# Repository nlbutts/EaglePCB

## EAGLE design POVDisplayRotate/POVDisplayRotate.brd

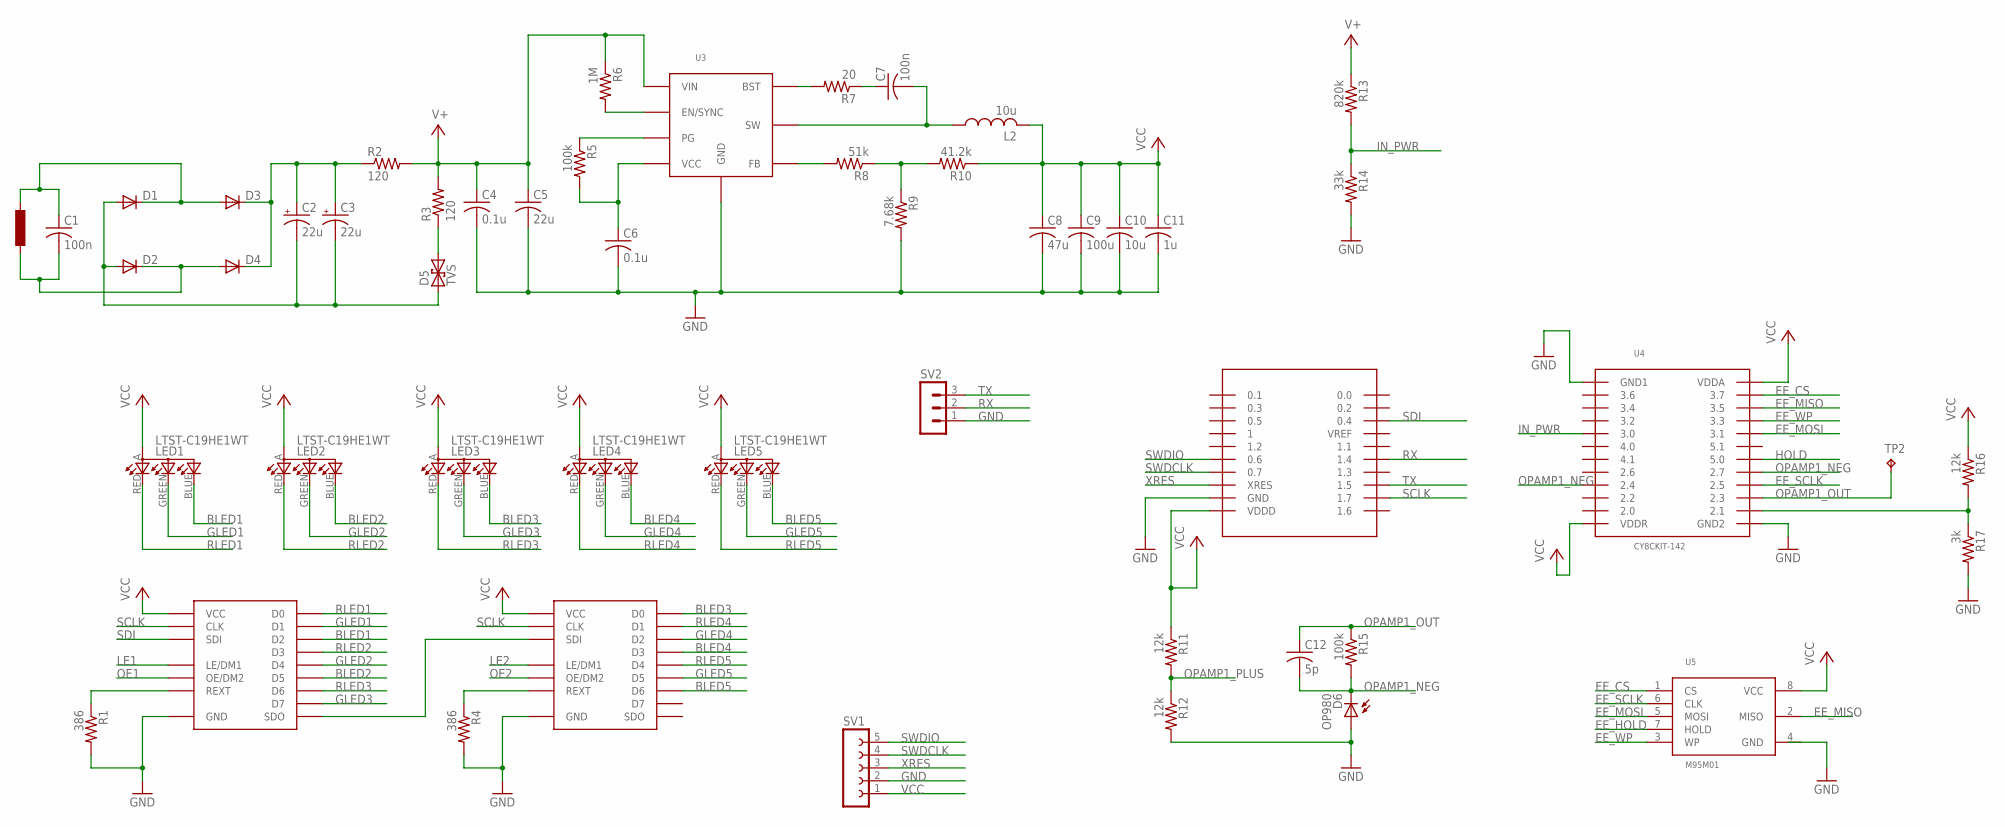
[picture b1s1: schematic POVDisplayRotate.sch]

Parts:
C1: 100n; C1210
C2, C3: 22u; PANASONIC_C; DIGIKEY PCE5022CT-ND
C4, C6: 0.1u; C0603; DIGIKEY 490-6505-1-ND
C5: 22u; C0805; DIGIKEY 445-14428-1-ND
C7: 100n; C0603
C8: 47u; C0603
C9: 100u; C1210
C10: 10u; C0603
C11: 1u; C0603
C12: 5p; C0603
D1, D2, D3, D4: DIODE-SOD123; SOD123; DIGIKEY B0540W-FDICT-ND
D5: TVS; SMB; DIGIKEY 1SMB28CAT3GOSCT-ND
D6: OP980; PLCC-2; DIGIKEY 365-1908-1-ND
L2: 10u; L1812; DIGIKEY 587-1625-1-ND
LED1, LED2, LED3, LED4, LED5: LTST-C19HE1WT; DIGIKEY 160-2162-1-ND
R1, R4: 386; R0603; DIGIKEY P0.0GCT-ND
R2, R3: 120; R0603; DIGIKEY P0.0GCT-ND
R5, R15: 100k; R0603; DIGIKEY P0.0GCT-ND
R6: 1M; R0603; DIGIKEY P0.0GCT-ND
R7: 20; R0603; DIGIKEY P0.0GCT-ND
R8: 51k; R0603; DIGIKEY P0.0GCT-ND
R9: 7.68k; R0603; DIGIKEY P0.0GCT-ND
R10: 41.2k; R0603; DIGIKEY P0.0GCT-ND
R11, R12, R16: 12k; R0603; DIGIKEY P0.0GCT-ND
R13: 820k; R0603; DIGIKEY P0.0GCT-ND
R14: 33k; R0603; DIGIKEY P0.0GCT-ND
R17: 3k; R0603; DIGIKEY P0.0GCT-ND
SV1: FE05-1
SV2: MA03-1
TP2: TPB1,27; B1,27
U1, U2: STP08DP05; SSOP16_EPAD; DIGIKEY 497-6119-1-ND
U3: MPQ4420Q; SOT-23-8; DIGIKEY 1589-1293-1-ND
U4: CY8CKIT-142
U5: M95M01; SO-08; DIGIKEY 497-14359-1-ND

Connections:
BLED1: LED1.BLUE (CBLUE), U1.7 (D2)
BLED2: LED2.BLUE (CBLUE), U1.10 (D5)
BLED3: LED3.BLUE (CBLUE), U2.5 (D0)
BLED4: LED4.BLUE (CBLUE), U2.8 (D3)
BLED5: LED5.BLUE (CBLUE), U2.11 (D6)
DAC_OUT: R16.2, R17.1, U4.2.1
EE_CS: U4.3.7, U5.1 (CS)
EE_HOLD: U5.7 (HOLD)
EE_MISO: U4.3.5, U5.2 (MISO)
EE_MOSI: U4.3.1, U5.5 (MOSI)
EE_SCLK: U4.2.5, U5.6 (CLK)
EE_WP: U4.3.3, U5.3 (WP)
GLED1: LED1.GREEN (CGREEN), U1.6 (D1)
GLED2: LED2.GREEN (CGREEN), U1.9 (D4)
GLED3: LED3.GREEN (CGREEN), U1.12 (D7)
GLED4: LED4.GREEN (CGREEN), U2.7 (D2)
GLED5: LED5.GREEN (CGREEN), U2.10 (D5)
GND: C4.2, C5.2, C6.2, C8.2, C9.2, C10.2, C11.2, D6.P$1 (A), R1.2, R4.2, R9.2, R12.2, R14.2, R17.2, SV1.2, SV2.1, U1.1 (GND), U1.GND, U2.1 (GND), U2.GND, U3.4 (GND), U4.GND, U4.GND1, U4.GND2, U5.4 (GND)
HOLD: U4.5.0
IN_PWR: R13.2, R14.1, U4.3.0
LE1: U1.4 (LE/DM1)
LE2: U2.4 (LE/DM1)
unnamed: C6.1, R5.2, U3.7 (VCC)
unnamed: R6.2, U3.6 (EN/SYNC)
unnamed: C2.+, C3.+, D3.C, D4.C, R2.1
unnamed: R8.2, U3.8 (FB)
unnamed: R8.1, R9.1, R10.2
unnamed: R1.1, U1.15 (REXT)
unnamed: R7.2, U3.5 (BST)
unnamed: C7.1, R7.1
unnamed: R4.1, U2.15 (REXT)
unnamed: D5.C (2), R3.1
unnamed: R5.1, U3.1 (PG)
unnamed: C2.-, C3.-, D1.A, D2.A, D5.A (1)
unnamed: U1.14 (SDO), U2.2 (SDI)
NEG_COIL: C1.2, D2.C, D4.A
OE1: U1.13 (OE/DM2)
OE2: U2.13 (OE/DM2)
OPAMP1_NEG: C12.2, D6.P$2 (C), R15.2, U4.2.4, U4.2.7
OPAMP1_OUT: C12.1, R15.1, TP2.TP, U4.2.3
OPAMP1_PLUS: R11.2, R12.1
POS_COIL: C1.1, D1.C, D3.A
RLED1: LED1.RED (CRED), U1.5 (D0)
RLED2: LED2.RED (CRED), U1.8 (D3)
RLED3: LED3.RED (CRED), U1.11 (D6)
RLED4: LED4.RED (CRED), U2.6 (D1)
RLED5: LED5.RED (CRED), U2.9 (D4)
RX: SV2.2, U4.1.4
SCLK: U1.3 (CLK), U2.3 (CLK), U4.1.7
SDI: U1.2 (SDI), U4.0.4
SWDCLK: SV1.4, U4.0.7
SWDIO: SV1.5, U4.0.6
SWOUT: C7.2, L2.1, U3.3 (SW)
TX: SV2.3, U4.1.5
V+: C4.1, C5.1, R2.2, R3.2, R6.1, R13.1, U3.2 (VIN)
VCC: C8.1, C9.1, C10.1, C11.1, L2.2, LED1.A, LED2.A, LED3.A, LED4.A, LED5.A, R10.1, R11.1, R16.1, SV1.1, U1.16 (VCC), U2.16 (VCC), U4.VDDA, U4.VDDD, U4.VDDR, U5.8 (VCC)
XRES: SV1.3, U4.XRES

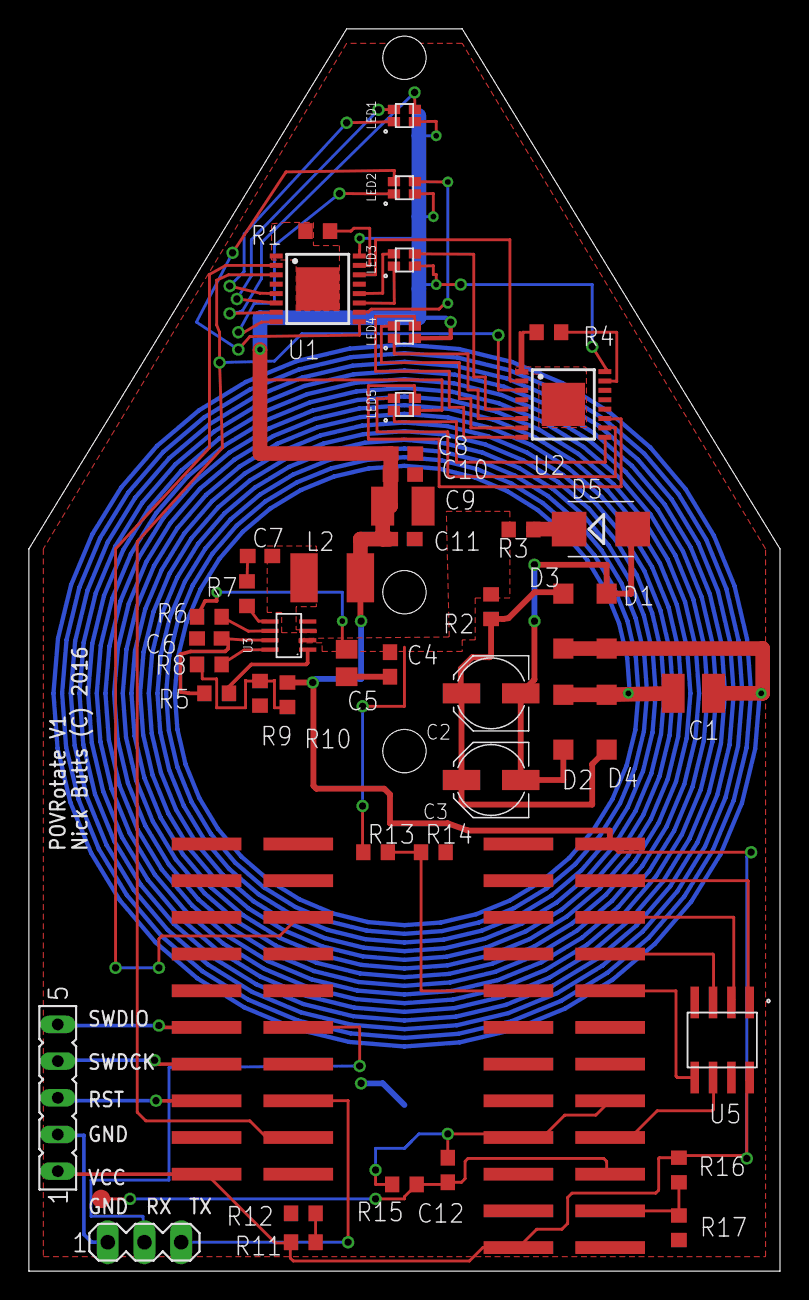
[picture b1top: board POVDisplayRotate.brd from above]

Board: 2 copper layers, 52.0 x 86.0 mm, 49 parts (1 on the bottom side), 51 nets.

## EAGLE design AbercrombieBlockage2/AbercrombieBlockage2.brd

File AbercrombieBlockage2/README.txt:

This is deprecated and has been moved to the Bitbucket Appareo location.

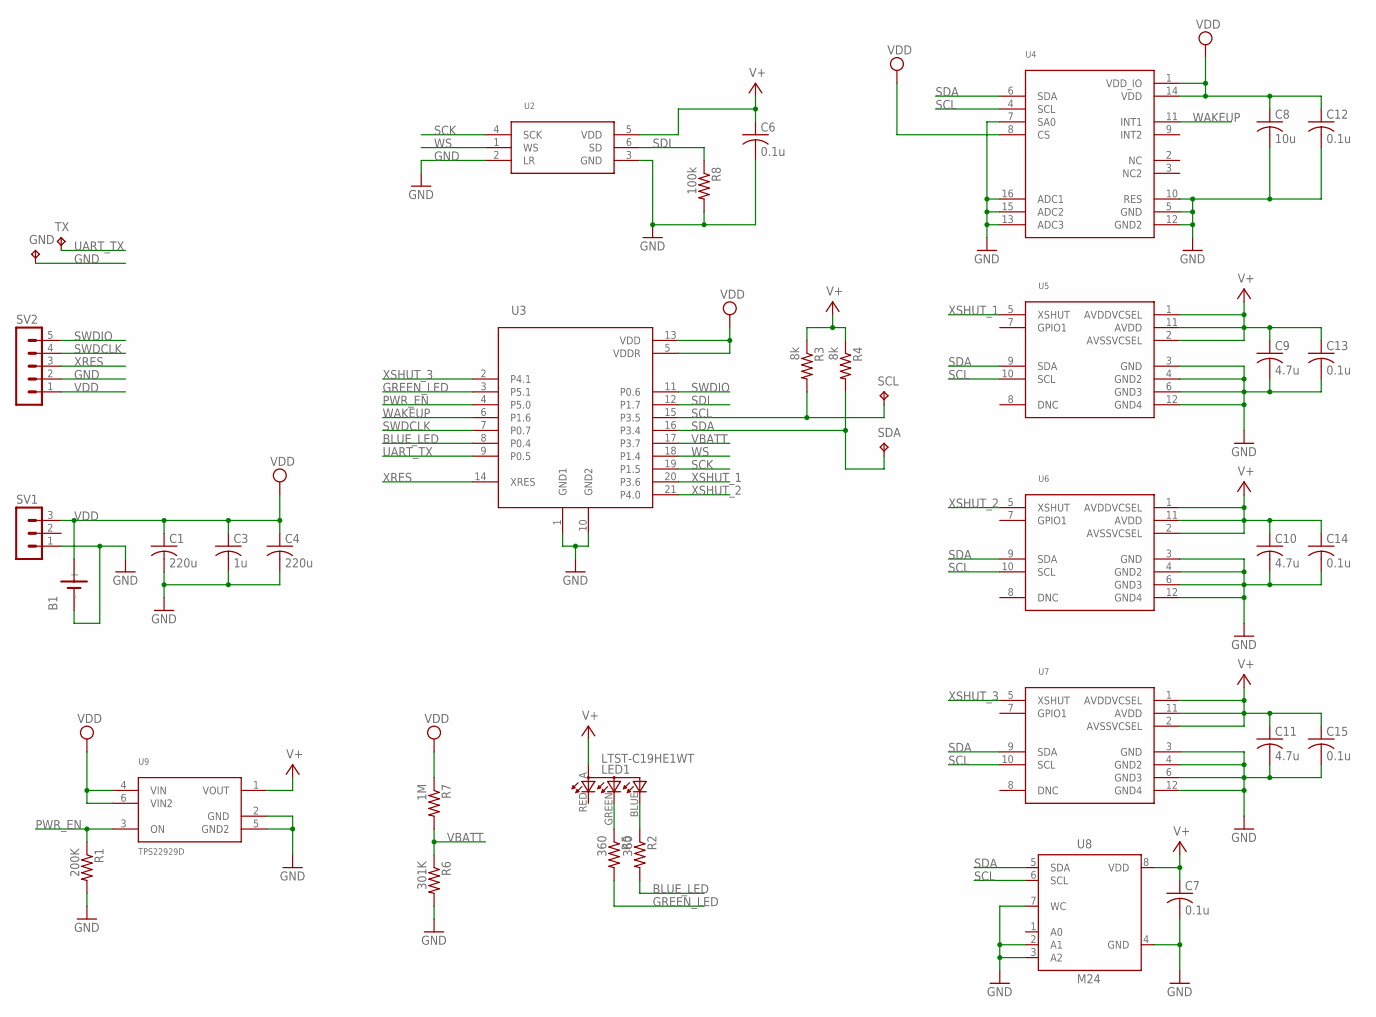
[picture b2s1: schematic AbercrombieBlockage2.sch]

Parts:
B1: BU2032
C1: 220u; C1210; DIGIKEYY 490-13250-1-ND
C3: 1u; C0603
C4: 220u; C1210
C6, C7, C12, C13, C14, C15: 0.1u; C0603
C8: 10u; C0603
C9, C10, C11: 4.7u; C0603
GND: TPB1,27; B1,27
LED1: LTST-C19HE1WT; DIGIKEY 160-2162-1-ND
R1: 200K; R0603
R2, R5: 360; R0603
R3, R4: 8k; R0603
R6: 301K; R0603
R7: 1M; R0603
R8: 100k; R0603
SCL: TPB1,27; B1,27
SDA: TPB1,27; B1,27
SV1: MA03-1
SV2: MA05-1; DIGIKEY 952-2246-ND
TX: TPB1,27; B1,27
U2: ICS-43434; DIGIKEY 1428-1066-1-ND
U3: CYBLE-022001-00; DIGIKEY 428-3566-PROMO-ND
U4: LIS3DH; LGA-16; DIGIKEY 497-10613-1-ND
U5, U6, U7: VL53L0X; DIGIKEY 497-16538-1-ND
U8: M24; SO-08; DIGIKEY 497-6351-1-ND
U9: TPS22929D; SOT-23-6

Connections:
BLUE_LED: R2.2, U3.8 (P0.4)
GND: B1.NEG (-), C1.2, C3.2, C4.2, C6.2, C7.2, C8.2, C9.2, C10.2, C11.2, C12.2, C13.2, C14.2, C15.2, GND.TP, R1.2, R6.2, R8.2, SV1.1, SV2.2, U2.2 (LR), U2.3 (GND), U3.1 (GND1), U3.10 (GND2), U4.5 (GND), U4.7 (SA0), U4.10 (RES), U4.12 (GND2), U4.13 (ADC3), U4.15 (ADC2), U4.16 (ADC1), U5.3 (GND), U5.4 (GND2), U5.6 (GND3), U5.12 (GND4), U6.3 (GND), U6.4 (GND2), U6.6 (GND3), U6.12 (GND4), U7.3 (GND), U7.4 (GND2), U7.6 (GND3), U7.12 (GND4), U8.2 (A1), U8.3 (A2), U8.4 (GND), U8.7 (WC), U9.2 (GND), U9.5 (GND2)
GREEN_LED: R5.2, U3.3 (P5.1)
unnamed: LED1.BLUE (CBLUE), R2.1
unnamed: LED1.GREEN (CGREEN), R5.1
PWR_EN: R1.1, U3.4 (P5.0), U9.3 (ON)
SCK: U2.4 (SCK), U3.19 (P1.5)
SCL: R3.2, SCL.TP, U3.15 (P3.5), U4.4 (SCL), U5.10 (SCL), U6.10 (SCL), U7.10 (SCL), U8.6 (SCL)
SDA: R4.2, SDA.TP, U3.16 (P3.4), U4.6 (SDA), U5.9 (SDA), U6.9 (SDA), U7.9 (SDA), U8.5 (SDA)
SDI: R8.1, U2.6 (SD), U3.12 (P1.7)
SWDCLK: SV2.4, U3.7 (P0.7)
SWDIO: SV2.5, U3.11 (P0.6)
UART_TX: TX.TP, U3.9 (P0.5)
V+: C6.1, C7.1, C9.1, C10.1, C11.1, C13.1, C14.1, C15.1, LED1.A, R3.1, R4.1, U2.5 (VDD), U5.1 (AVDDVCSEL), U5.2 (AVSSVCSEL), U5.11 (AVDD), U6.1 (AVDDVCSEL), U6.2 (AVSSVCSEL), U6.11 (AVDD), U7.1 (AVDDVCSEL), U7.2 (AVSSVCSEL), U7.11 (AVDD), U8.8 (VDD), U9.1 (VOUT)
VBATT: R6.1, R7.2, U3.17 (P3.7)
VDD: B1.PLUS (+), C1.1, C3.1, C4.1, C8.1, C12.1, R7.1, SV1.3, SV2.1, U3.5 (VDDR), U3.13 (VDD), U4.1 (VDD_IO), U4.8 (CS), U4.14 (VDD), U9.4 (VIN), U9.6 (VIN2)
WAKEUP: U3.6 (P1.6), U4.11 (INT1)
WS: U2.1 (WS), U3.18 (P1.4)
XRES: SV2.3, U3.14 (XRES)
XSHUT_1: U3.20 (P3.6), U5.5 (XSHUT)
XSHUT_2: U3.21 (P4.0), U6.5 (XSHUT)
XSHUT_3: U3.2 (P4.1), U7.5 (XSHUT)

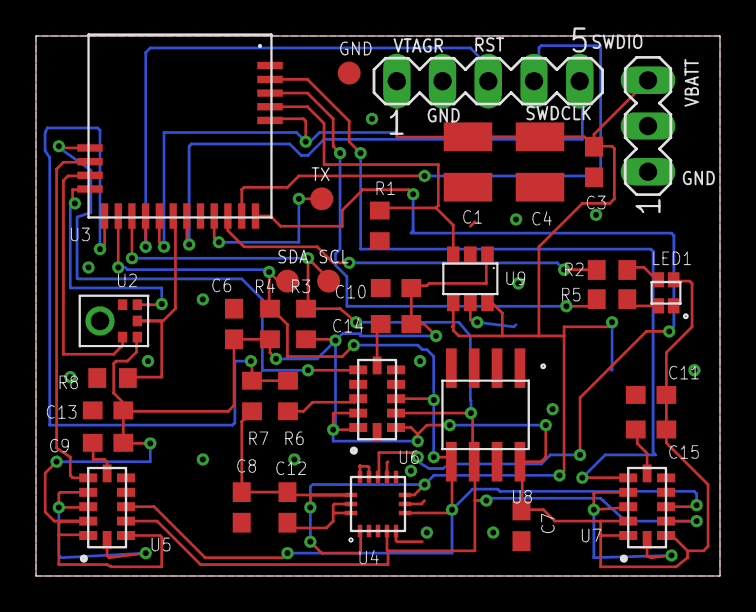
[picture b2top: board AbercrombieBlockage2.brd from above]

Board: 2 copper layers, 38.0 x 30.0 mm, 37 parts (1 on the bottom side), 22 nets.

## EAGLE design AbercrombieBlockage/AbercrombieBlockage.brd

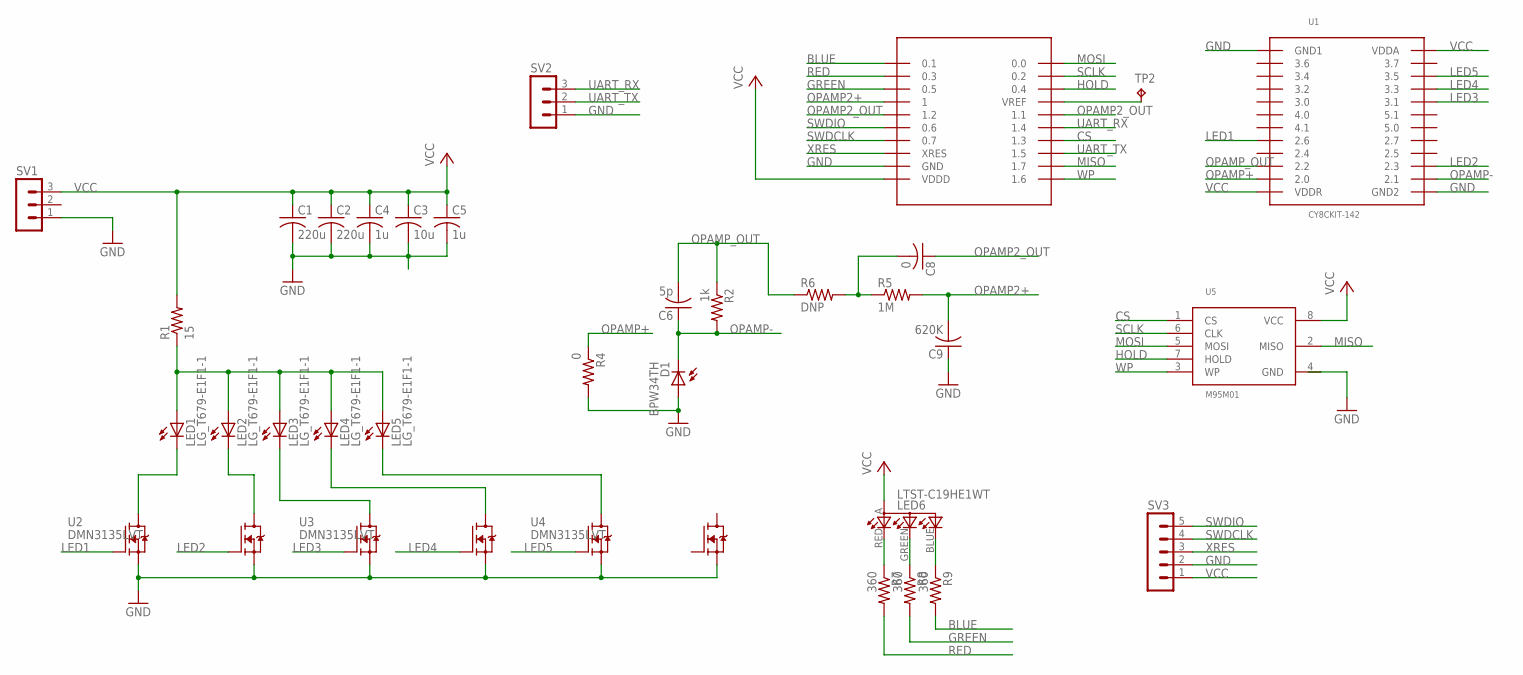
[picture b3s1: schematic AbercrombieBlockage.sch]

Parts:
C1, C2: 220u; C1210
C3: 10u; C1210
C4, C5: 1u; C0603
C6: 5p; C0603
C8: 0; C0603
C9: 620K; C0603
D1: BPW34TH; BPW34
LED1, LED2, LED3, LED4, LED5: LG_T679-E1F1-1; PLCC2; DIGIKEY VSMY3850-GS08CT-ND
LED6: LTST-C19HE1WT
R1: 15; R2010; DIGIKEY_100_OHM YAG3381CT-ND
R2: 1k; R0603
R4: 0; R0603
R5: 1M; R0603
R6: DNP; R0603
R7, R8, R9: 360; R0603
SV1, SV2: MA03-1
SV3: MA05-1
TP2: TPB1,27; B1,27
U1: CY8CKIT-142
U2, U3, U4: DMN3135LVT; SOT-23-6; DIGIKEY DMN3135LVT-7DICT-ND
U5: M95M01; SO-08; DIGIKEY 497-14359-1-ND

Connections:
BLUE: R9.2, U1.0.1
CS: U1.1.3, U5.1 (CS)
GND: C1.2, C2.2, C3.2, C4.2, C5.2, C9.1, D1.A, R4.2, SV1.1, SV2.1, SV3.2, U1.GND, U1.GND1, U1.GND2, U2.2 (S2), U2.5 (S1), U3.2 (S2), U3.5 (S1), U4.2 (S2), U4.5 (S1), U5.4 (GND)
GREEN: R8.2, U1.0.5
HOLD: U1.0.4, U5.7 (HOLD)
LED1: U1.2.6, U2.1 (G1)
LED2: U1.2.3, U2.3 (G2)
LED3: U1.3.1, U3.1 (G1)
LED4: U1.3.3, U3.3 (G2)
LED5: U1.3.5, U4.1 (G1)
MISO: U1.1.7, U5.2 (MISO)
MOSI: U1.0.0, U5.5 (MOSI)
unnamed: LED1.A, LED2.A, LED3.A, LED4.A, LED5.A, R1.1
unnamed: LED1.C, U2.6 (D1)
unnamed: LED2.C, U2.4 (D2)
unnamed: LED3.C, U3.6 (D1)
unnamed: LED4.C, U3.4 (D2)
unnamed: LED5.C, U4.6 (D1)
unnamed: C8.2, R5.1, R6.2
unnamed: TP2.TP, U1.VREF
unnamed: LED6.RED (CRED), R7.1
unnamed: LED6.GREEN (CGREEN), R8.1
unnamed: LED6.BLUE (CBLUE), R9.1
OPAMP2+: C9.2, R5.2, U1.1
OPAMP2_OUT: C8.1, U1.1.1, U1.1.2
OPAMP+: R4.1, U1.2.0
OPAMP-: C6.1, D1.C, R2.2, U1.2.1
OPAMP_OUT: C6.2, R2.1, R6.1, U1.2.2
RED: R7.2, U1.0.3
SCLK: U1.0.2, U5.6 (CLK)
SWDCLK: SV3.4, U1.0.7
SWDIO: SV3.5, U1.0.6
UART_RX: SV2.3, U1.1.4
UART_TX: SV2.2, U1.1.5
VCC: C1.1, C2.1, C3.1, C4.1, C5.1, LED6.A, R1.2, SV1.3, SV3.1, U1.VDDA, U1.VDDD, U1.VDDR, U5.8 (VCC)
WP: U1.1.6, U5.3 (WP)
XRES: SV3.3, U1.XRES

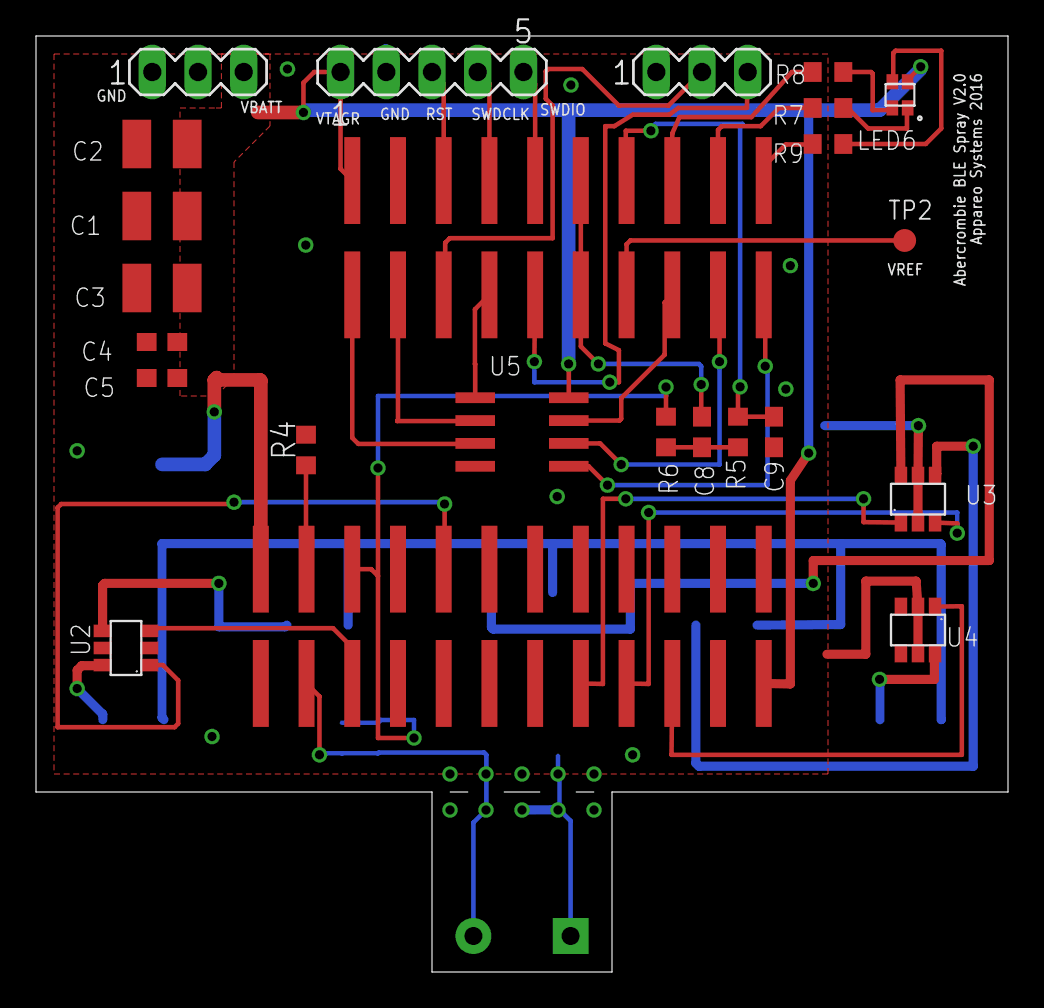
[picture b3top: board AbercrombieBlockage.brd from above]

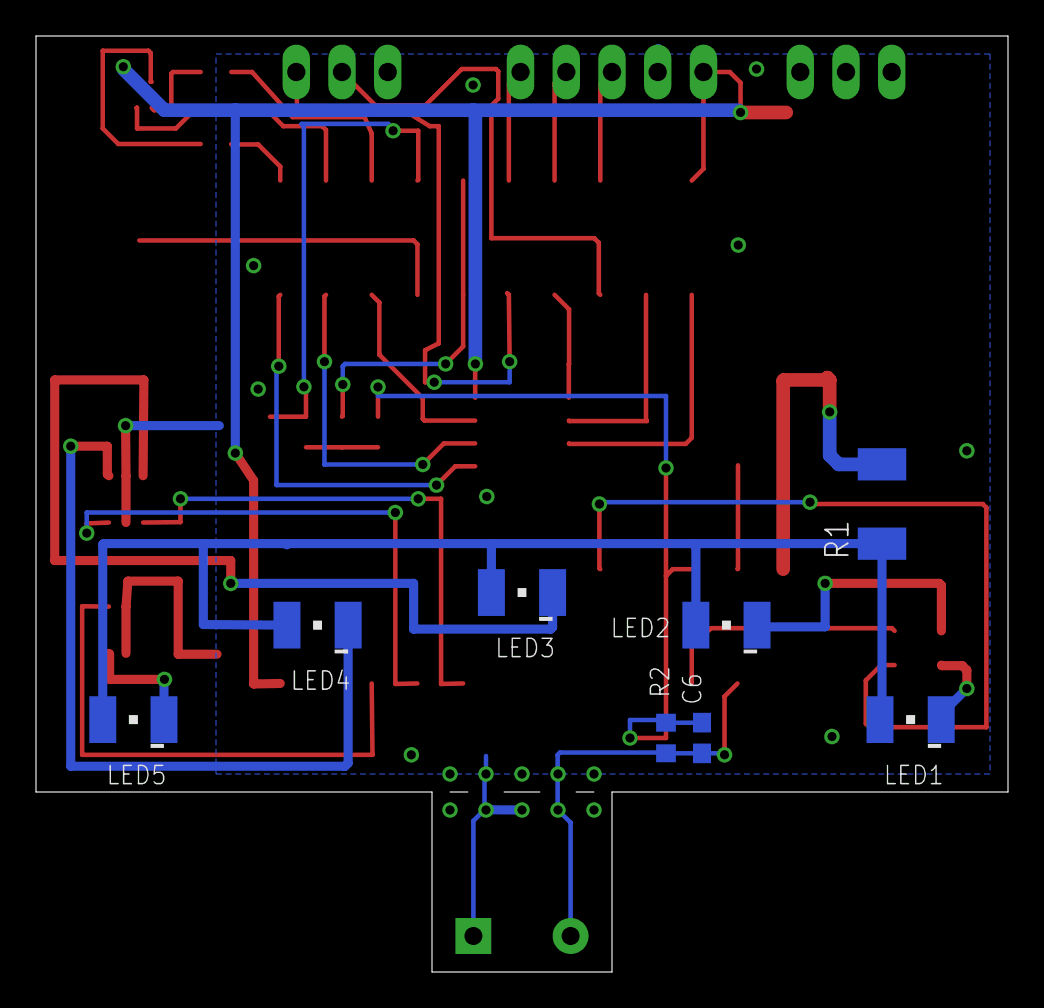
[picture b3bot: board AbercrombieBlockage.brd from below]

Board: 2 copper layers, 54.0 x 52.0 mm, 32 parts (9 on the bottom side), 37 nets.

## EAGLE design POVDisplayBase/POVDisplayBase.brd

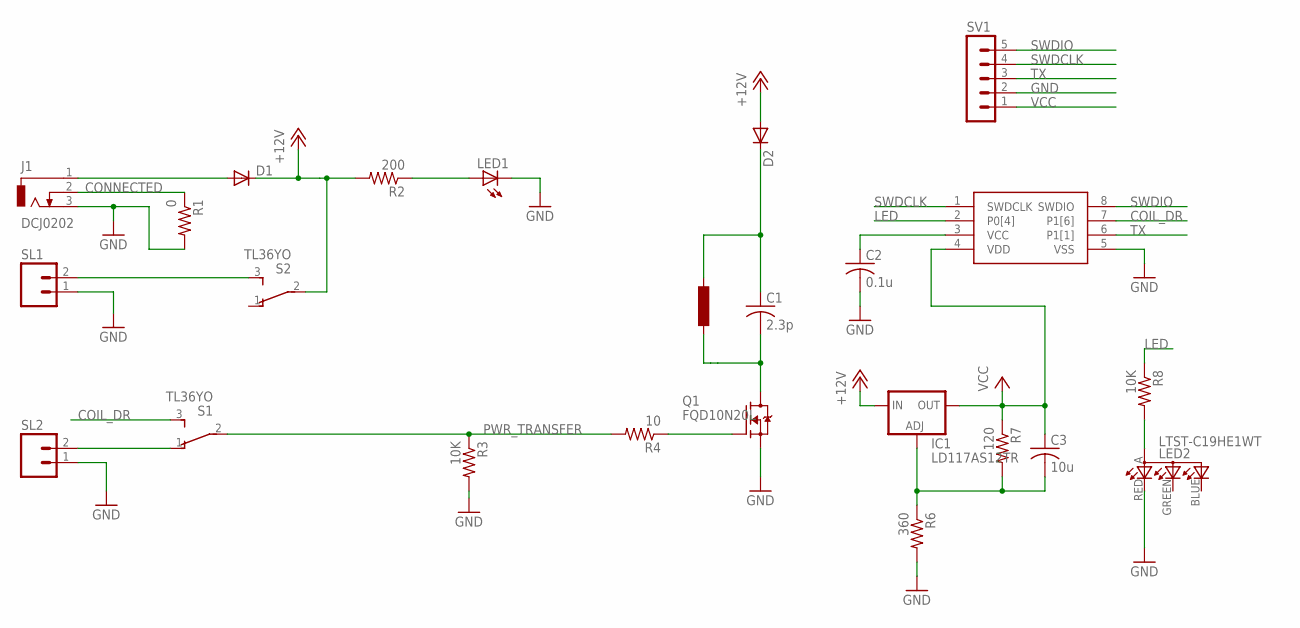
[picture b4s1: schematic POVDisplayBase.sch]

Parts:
C1: 2.3p; C1210
C2: 0.1u; C0603
C3: 10u; C0603
D1: DIODE-DO-214AC; DO-214AC; DIGIKEY 641-1707-1-ND
D2: DIODE-SMC; SMC; DIGIKEY S5KC-FDICT-ND
IC1: LD117AS12TR; SOT223
J1: DCJ0202; DIGIKEY CP-002B-ND
LED1: LEDCHIPLED_1206; CHIPLED_1206; DIGIKEY 1080-1346-1-ND
LED2: LTST-C19HE1WT
Q1: FQD10N20L; TO252; DIGIKEY FQD10N20LTMCT-ND
R1: 0; R0603; DIGIKEY P180GCT-ND
R2: 200; R0603; DIGIKEY P180GCT-ND
R3, R8: 10K; R0603; DIGIKEY P180GCT-ND
R4: 10; R0603; DIGIKEY P180GCT-ND
R6: 360; R0603; DIGIKEY P180GCT-ND
R7: 120; R0603; DIGIKEY P180GCT-ND
S1, S2: TL36YO; TL3XYO; DIGIKEY 450-1603-ND
SL1, SL2: M02; 02P
SV1: MA05-1
U1: CY8C4013SXI-400; SOIC08

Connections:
+12V: D1.C, D2.A, IC1.3 (IN), R2.2, S2.2
COIL_DR: S1.3 (S), U1.7 (P1[6])
CONNECTED: J1.2, R1.1
GND: C2.2, J1.3, LED1.C, LED2.RED (CRED), Q1.2 (S), R1.2, R3.2, R6.2, SL1.1, SL2.1, SV1.2, U1.5 (VSS)
LED: R8.1, U1.2 (P0[4])
unnamed: Q1.1 (G), R4.1
unnamed: LED1.A, R2.1
unnamed: S2.3 (S), SL1.2
unnamed: D1.A, J1.1
unnamed: C3.2, IC1.1 (ADJ), R6.1, R7.2
unnamed: LED2.A, R8.2
unnamed: C2.1, U1.3 (VCC)
unnamed: S1.1 (O), SL2.2
NEG_COIL: C1.2, Q1.3 (D)
POS_COIL: C1.1, D2.C
PWR_TRANSFER: R3.1, R4.2, S1.2
SWDCLK: SV1.4, U1.1 (SWDCLK)
SWDIO: SV1.5, U1.8 (SWDIO)
TX: SV1.3, U1.6 (P1[1])
VCC: C3.1, IC1.4 (OUT), R7.1, SV1.1, U1.4 (VDD)

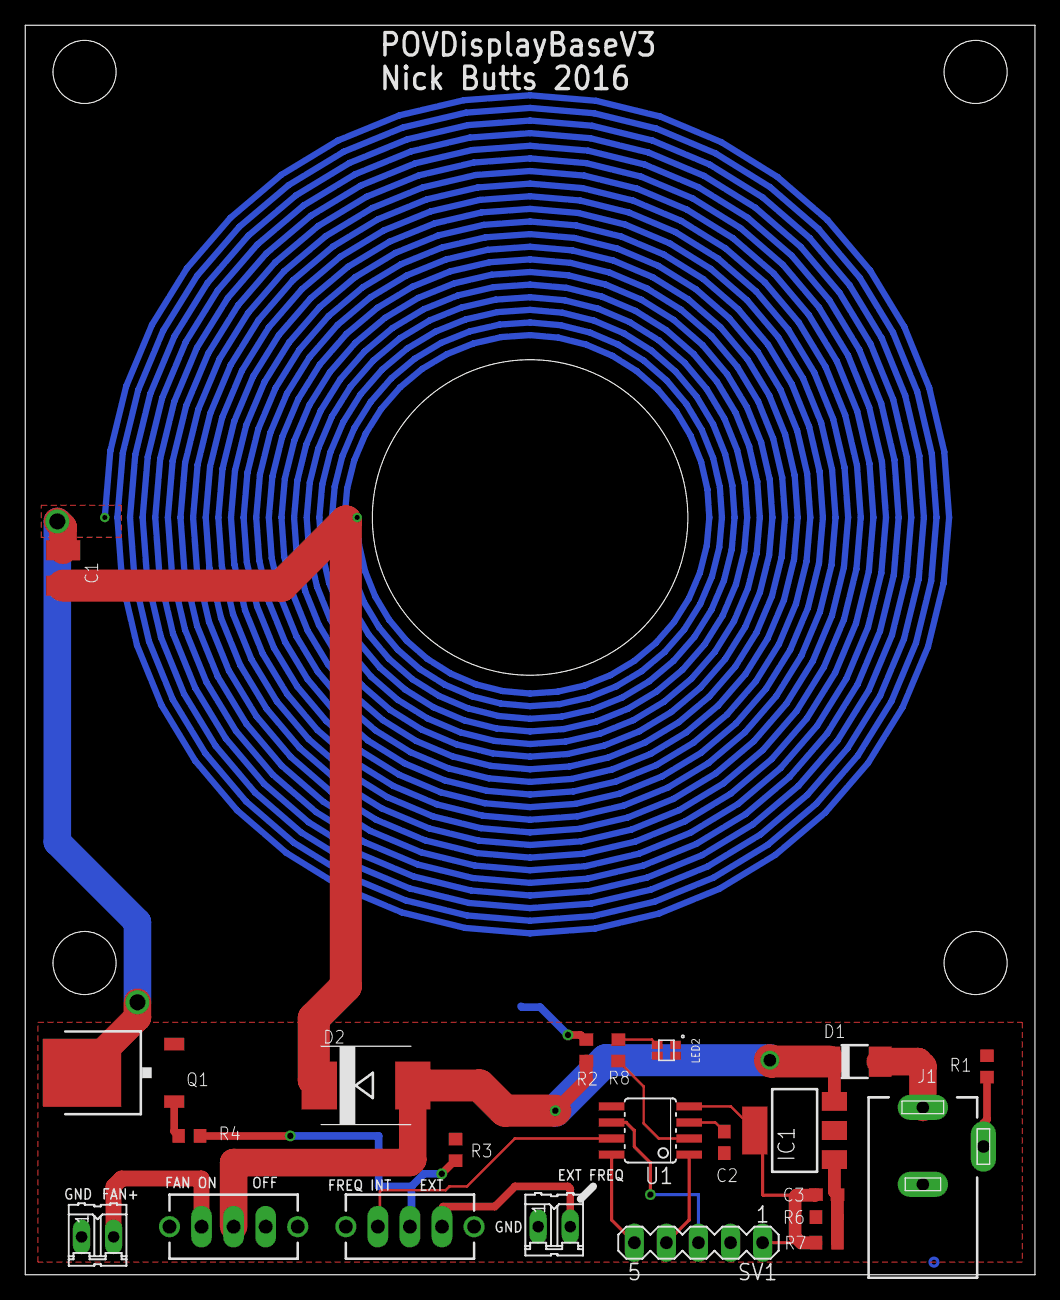
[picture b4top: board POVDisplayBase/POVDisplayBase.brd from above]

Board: 2 copper layers, 80.0 x 99.0 mm, 23 parts (1 on the bottom side), 20 nets.

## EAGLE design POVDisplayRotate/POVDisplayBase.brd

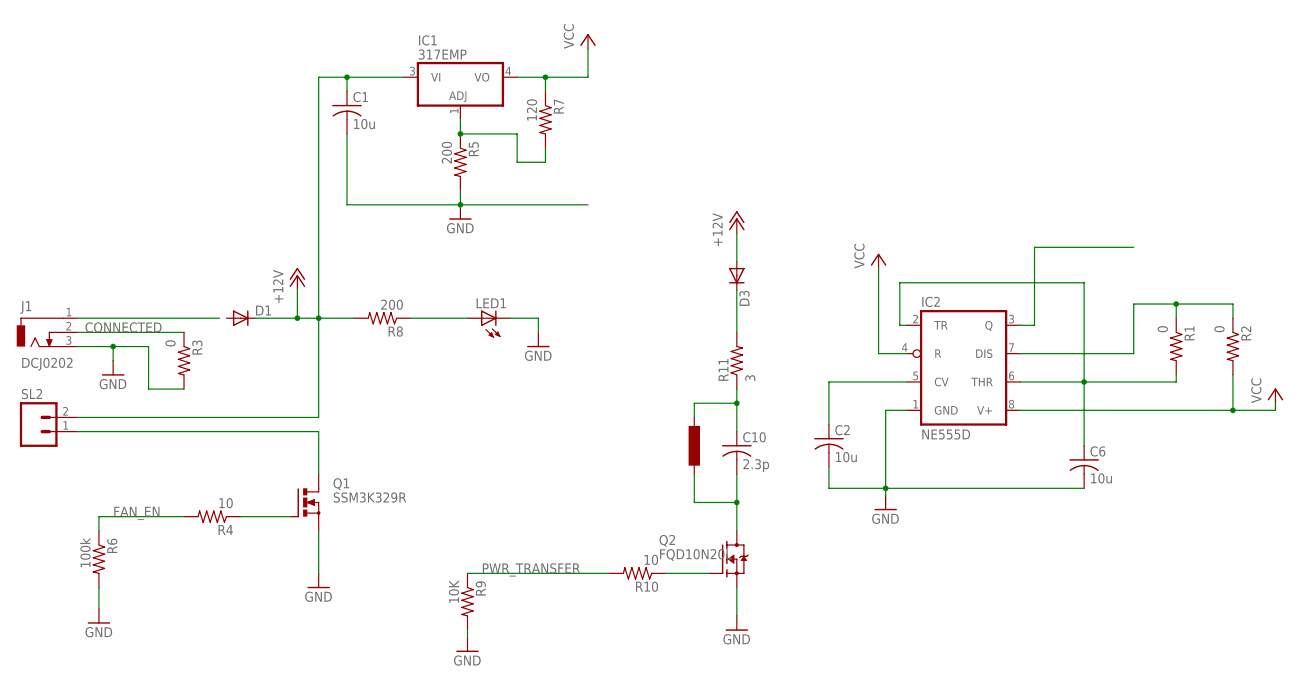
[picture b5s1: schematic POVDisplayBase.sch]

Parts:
C1, C2, C6: 10u; C0603
C10: 2.3p; C1210
D1: DIODE-DO-214AC; DO-214AC; DIGIKEY 641-1707-1-ND
D3: DIODE-SMC; SMC; DIGIKEY S5KC-FDICT-ND
IC1: 317EMP; SOT223; DIGIKEY 497-4241-1-ND
IC2: NE555D; SO08
J1: DCJ0202; DIGIKEY CP-002B-ND
LED1: LEDCHIPLED_1206; CHIPLED_1206; DIGIKEY 1080-1346-1-ND
Q1: SSM3K329R; SOT23
Q2: FQD10N20L; TO252; DIGIKEY FQD10N20LTMCT-ND
R1, R2, R3: 0; R0603; DIGIKEY P180GCT-ND
R4: 10; R0603; DIGIKEY P100KGCT-ND
R5: 200; R0603; DIGIKEY P0.0GCT-ND
R6: 100k; R0603; DIGIKEY P0.0GCT-ND
R7: 120; R0603; DIGIKEY P0.0GCT-ND
R8: 200; R0603; DIGIKEY P180GCT-ND
R9: 10K; R0603; DIGIKEY P180GCT-ND
R10: 10; R0603; DIGIKEY P180GCT-ND
R11: 3; R1210
SL2: M02; 02P

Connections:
+12V: C1.1, D1.C, D3.A, IC1.3 (VI), R8.2, SL2.2
CONNECTED: J1.2, R3.1
FAN_EN: R4.2, R6.1
GND: C1.2, C2.2, C6.2, IC2.1 (GND), J1.3, LED1.C, Q1.2 (S), Q2.2 (S), R3.2, R5.2, R6.2, R9.2
unnamed: Q2.1 (G), R10.1
unnamed: LED1.A, R8.1
unnamed: Q1.3 (D), SL2.1
unnamed: C6.1, IC2.2 (TR), IC2.6 (THR), R1.2
unnamed: IC1.1 (ADJ), R5.1, R7.2
unnamed: IC2.7 (DIS), R1.1, R2.1
unnamed: Q1.1 (G), R4.1
unnamed: D3.C, R11.2
unnamed: C2.1, IC2.5 (CV)
NEG_COIL: C10.2, Q2.3 (D)
POS_COIL: C10.1, R11.1
PWR_TRANSFER: R9.1, R10.2
VCC: IC1.4 (VO), IC2.4 (R), IC2.8 (V+), R2.2, R7.1

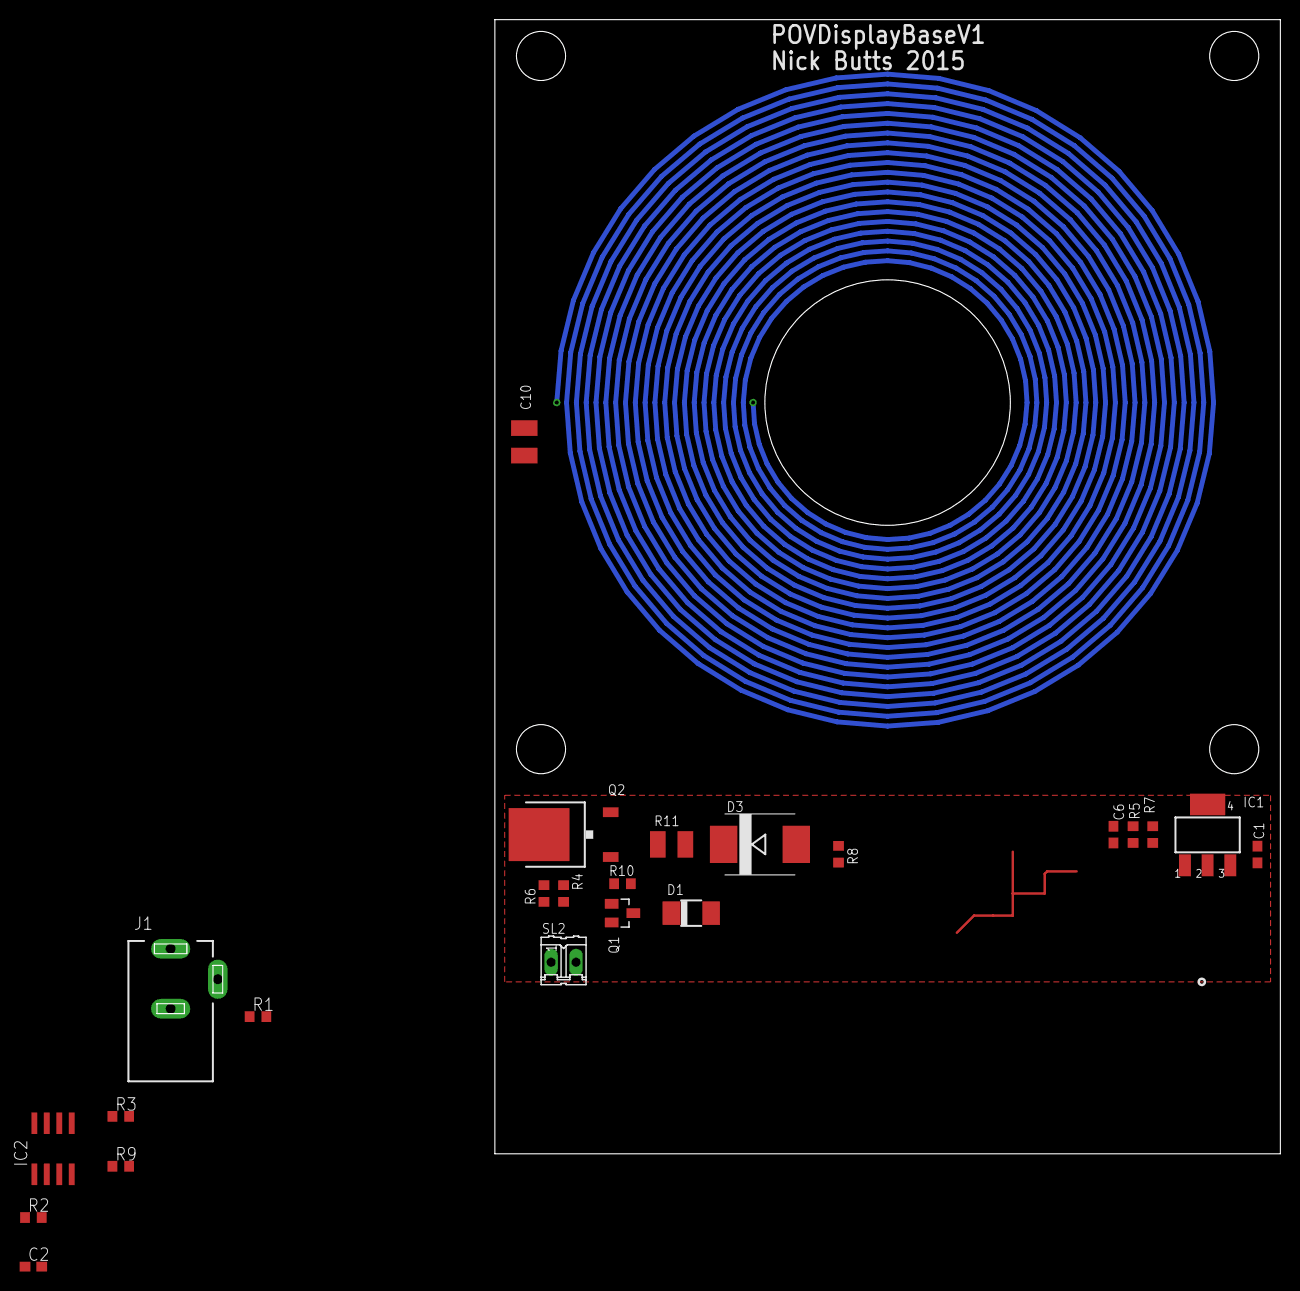
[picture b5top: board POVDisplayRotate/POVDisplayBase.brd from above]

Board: 2 copper layers, 114.7 x 115.5 mm, 24 parts (1 on the bottom side), 17 nets.

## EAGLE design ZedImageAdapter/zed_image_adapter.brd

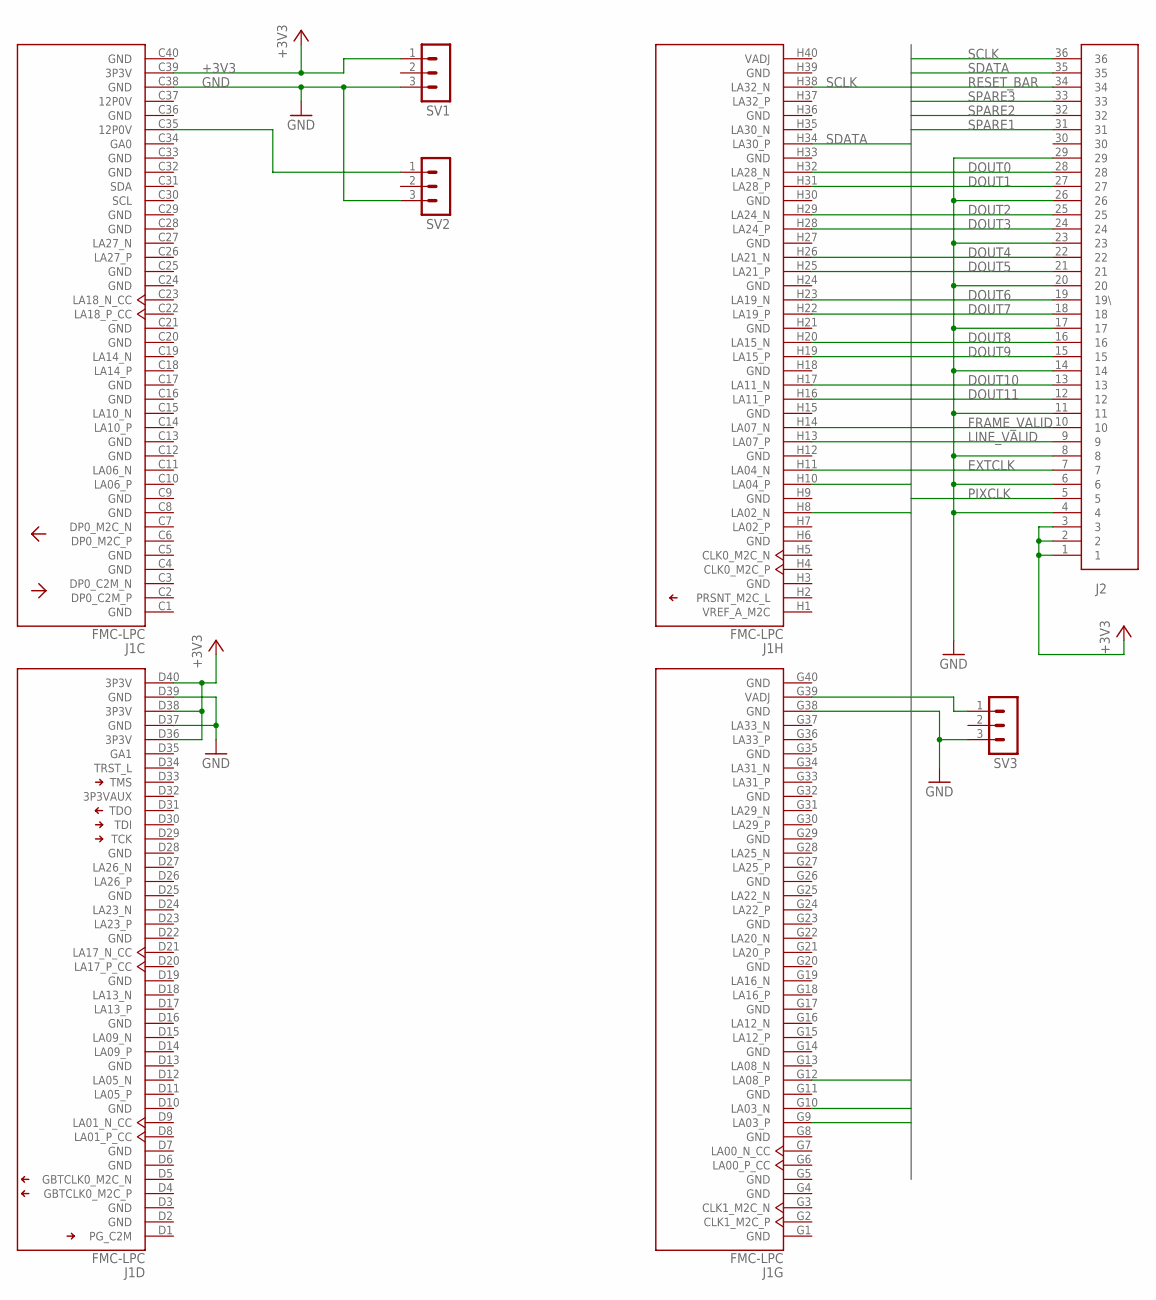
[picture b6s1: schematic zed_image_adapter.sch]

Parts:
J1: FMC-LPC; FMC-LPC-MALE
J2: MOLEX_54132_3662
SV1, SV2, SV3: MA03-1

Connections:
+3V3: J1.C39 (3P3V), J1.D36 (3P3V), J1.D38 (3P3V), J1.D40 (3P3V), J2.1, J2.2, J2.3, SV1.1
DOUT0: J1.H26 (LA21_N), J2.28
DOUT1: J1.H25 (LA21_P), J2.27
DOUT2: J1.H23 (LA19_N), J2.25
DOUT3: J1.H22 (LA19_P), J2.24
DOUT4: J1.H20 (LA15_N), J2.22
DOUT5: J1.H19 (LA15_P), J2.21
DOUT6: J1.H17 (LA11_N), J2.19 (19\)
DOUT7: J1.H16 (LA11_P), J2.18
DOUT8: J1.H14 (LA07_N), J2.16
DOUT9: J1.H13 (LA07_P), J2.15
DOUT10: J1.H11 (LA04_N), J2.13
DOUT11: J1.G9 (LA03_P), J2.12
EXTCLK: J1.H10 (LA04_P), J2.7
FRAME_VALID: J1.G10 (LA03_N), J2.10
GND: J1.C38 (GND), J1.D37 (GND), J1.D39 (GND), J1.G38 (GND), J2.4, J2.6, J2.8, J2.11, J2.14, J2.17, J2.20, J2.23, J2.26, J2.29, SV1.3, SV2.3, SV3.3
LINE_VALID: J1.G12 (LA08_P), J2.9
unnamed: J1.C35 (12P0V), SV2.1
unnamed: J1.G39 (VADJ), SV3.1
PIXCLK: J1.H8 (LA02_N), J2.5
RESET_BAR: J1.H32 (LA28_N), J2.34
SCLK: J1.H38 (LA32_N), J2.36
SDATA: J1.H34 (LA30_P), J2.35
SPARE1: J1.H31 (LA28_P), J2.31
SPARE2: J1.H29 (LA24_N), J2.32
SPARE3: J1.H28 (LA24_P), J2.33

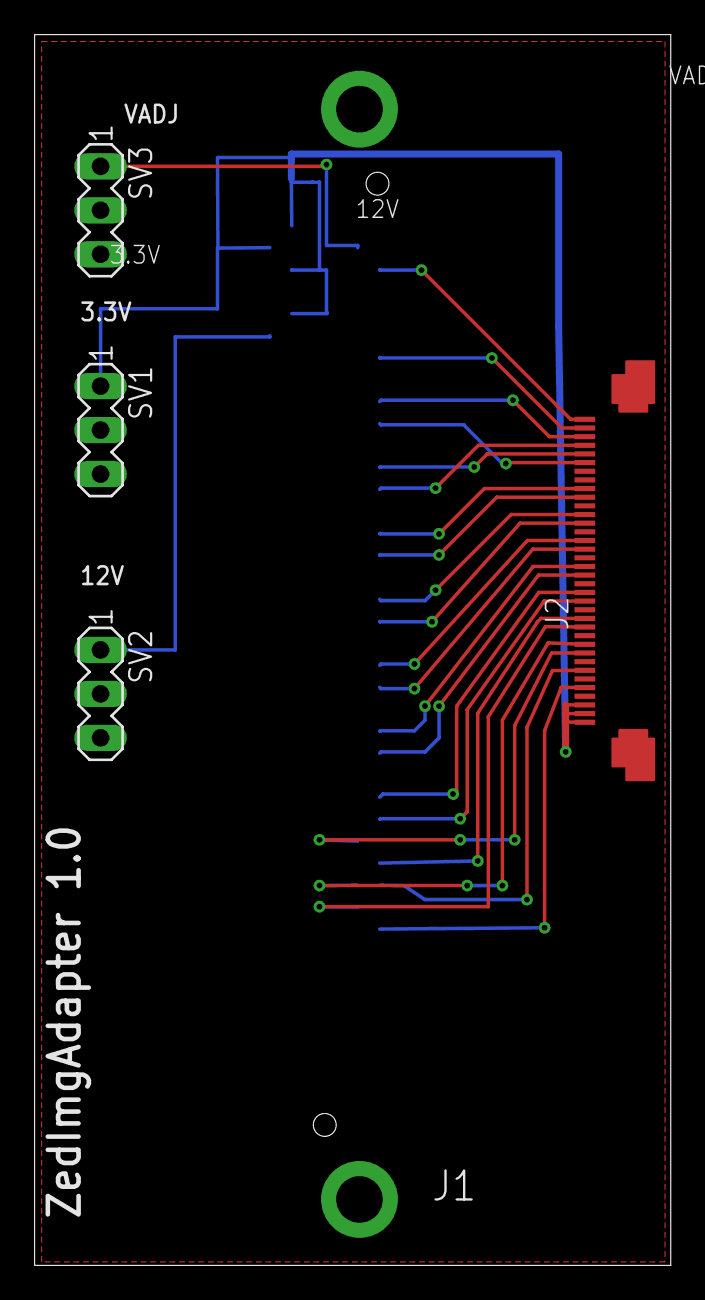
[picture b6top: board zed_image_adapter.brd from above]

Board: 2 copper layers, 36.8 x 71.1 mm, 5 parts (0 on the bottom side), 26 nets.

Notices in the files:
POVDisplayRotate/POVDisplayRotate.brd:
Nick Butts (C) 2016
